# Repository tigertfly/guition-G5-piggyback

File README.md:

# Guition piggyback
Small add-on pcb that hooks to the SD card slot of Guition ESP32-S3-4848S040 development board to create a simulated standby flight instrument.

Inspired by [CC_G5 project by Chris Crawford](https://github.com/ccrawford/CC_G5), makes it possible to add an encoder and power button to the Guition development board without soldering.

## GPIO Pin Assignments 

The Guition development board uses four GPIO pins for the MicroSD card reader, that can be used for the simulated G5 functions.

| MobiFlight Device | GPIO |
|-------------------|------|
| Power button | GPIO 42 |
| Encoder button | GPIO 47 |
| Encoder A Pin | GPIO 48 |
| Encoder B Pin | GPIO 41 |

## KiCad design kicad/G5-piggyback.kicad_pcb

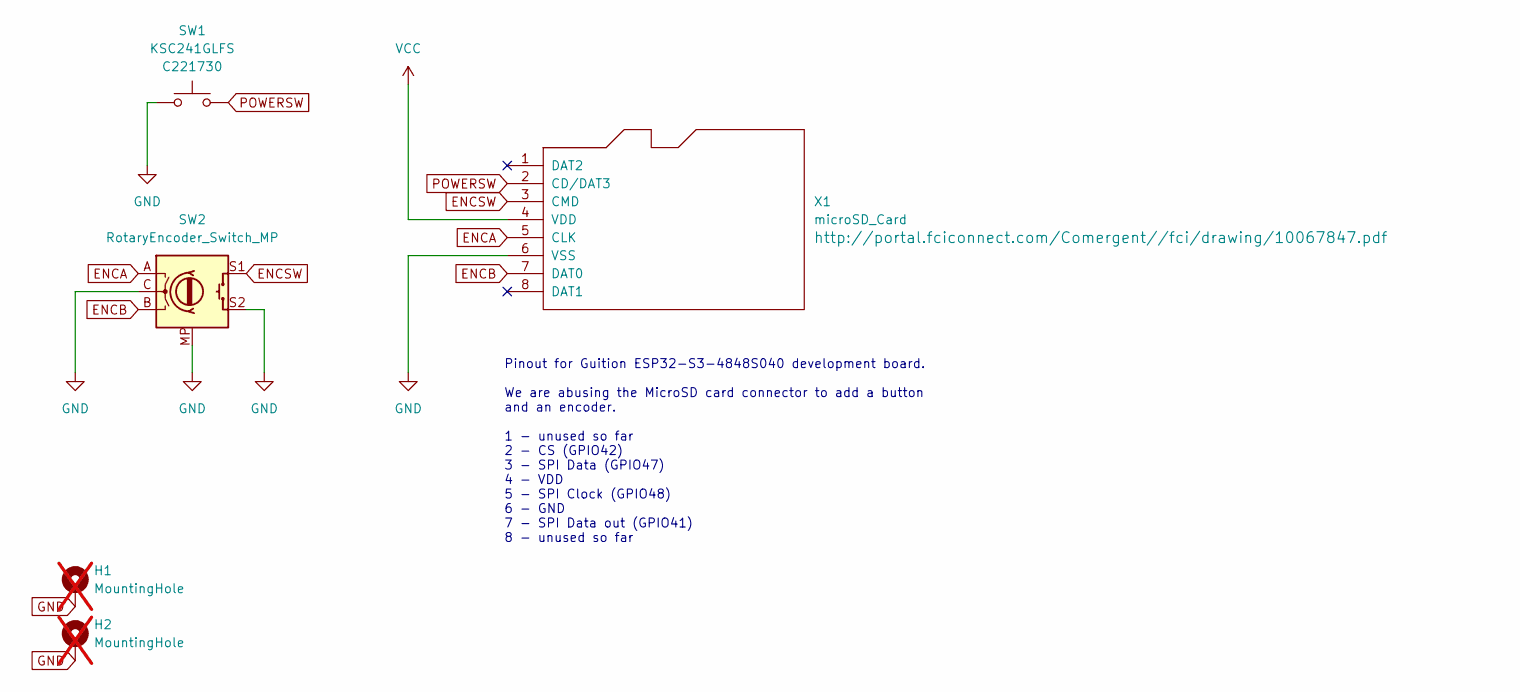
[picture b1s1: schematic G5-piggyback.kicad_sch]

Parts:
H1, H2: MountingHole; MountingHole_3.2mm_M3_ISO14580_Pad_TopBottom; not fitted
SW1: KSC241GLFS; LCSC Part # C221730
SW2: RotaryEncoder_Switch_MP; RotaryEncoder_Alps_EC11E-Switch_Vertical_H20mm_MountingHoles
X1: microSD_Card

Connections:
ENCA: SW2.A, X1.5 (CLK)
ENCB: SW2.B, X1.7 (DAT0)
ENCSW: SW2.S1, X1.3 (CMD)
GND: H1.1, H2.1, SW1.1, SW2.C, SW2.MP, SW2.S2, X1.6 (VSS)
POWERSW: SW1.2, X1.2 (CD/DAT3)
VCC: X1.4 (VDD)

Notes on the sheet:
Pinout for Guition ESP32-S3-4848S040 development board. We are abusing the MicroSD card connector to add a button and an encoder. 1 - unused so far 2 - CS (GPIO42) 3 - SPI Data (GPIO47) 4 - VDD 5 - SPI Clock (GPIO48) 6 - GND 7 - SPI Data out (GPIO41) 8 - unused so far

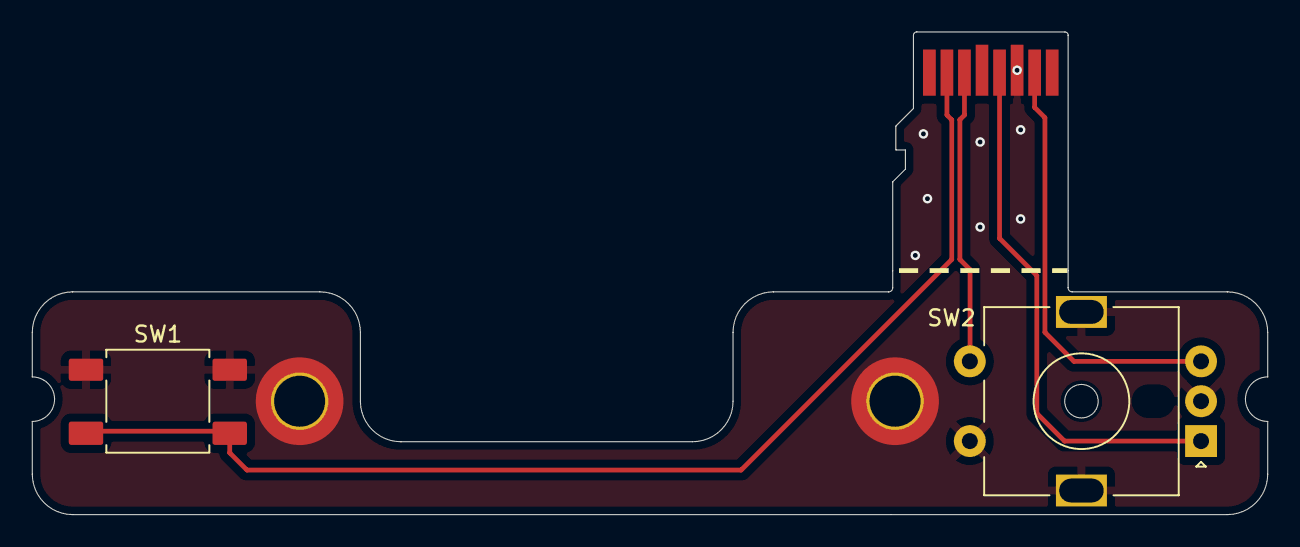
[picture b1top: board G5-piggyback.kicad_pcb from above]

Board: 2 copper layers, 77.5 x 30.2 mm, 5 parts (0 on the bottom side), 5 nets.

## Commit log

2025-11-25 Revise README title and add project inspiration
    Updated project title and added inspiration note.
2025-11-25 added photo of pcb
2025-11-25 Add visual reference image to README
    Included an image in the README to enhance visual understanding of the project.
2025-11-25 pcb project added
2025-11-25 Updated layout slightly: centered things vertically, added slightly more space between devboard case and pcb top edge so the microsd click mechanism can hopefully operate without disassembly.
2025-11-29 added table about gpio pins

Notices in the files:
kicad/G5-piggyback.kicad_pcb:
©2025 Tuomas Kuosmanen
